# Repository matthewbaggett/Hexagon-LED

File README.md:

# Hexagon LED

## Objective:

Build a small, inexpensive hexagonal lighting PCB with an inexpensive microcontroller that can communicate using slow-speed software serial
 with the other attached nodes and to an optionally fitted ESP8266 ESP-01 module which will designate itself the "host", 
 and populate out colour information from the center.
 
A serial mesh of communication between each interlinked hexagonal node.

A REST service running on the ESP sat on the users Wifi allowing for colour information to be pushed from an app or script.

## Render

## Board

Not shown: Groundplane fill. Represented by area inside red dashed octagon

Purple outline: Lasercut rear plastic panel to insert into the back of a 3d printed housing.

Illustration shows shielded 3x2 keyed connectors, not necessarily fitted.

## Schematic

### Microcontroller

### LEDs

### Interconnects

## License
This project is licensed under the The TAPR Open Hardware License.

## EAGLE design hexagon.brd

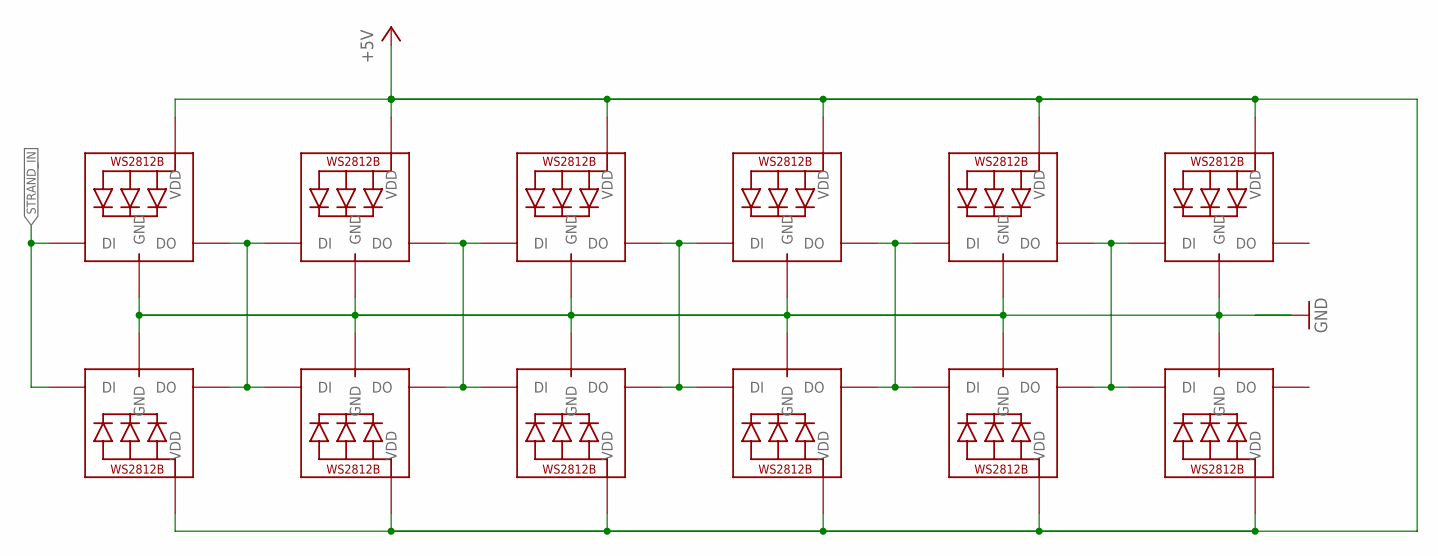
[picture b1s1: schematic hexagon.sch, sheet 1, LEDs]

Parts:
LED1, LED2, LED3, LED4, LED5, LED6: WS2812B5050; WS2812B
LED7, LED8, LED9, LED10, LED11, LED12: WS2812B3535; LED3535

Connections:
+5V: LED1.1-VDD (VDD), LED2.1-VDD (VDD), LED3.1-VDD (VDD), LED4.1-VDD (VDD), LED5.1-VDD (VDD), LED6.1-VDD (VDD), LED7.2 (VDD), LED8.2 (VDD), LED9.2 (VDD), LED10.2 (VDD), LED11.2 (VDD), LED12.2 (VDD); also elsewhere on the board
GND: LED1.3-GND (GND), LED2.3-GND (GND), LED3.3-GND (GND), LED4.3-GND (GND), LED5.3-GND (GND), LED6.3-GND (GND), LED7.4 (GND), LED8.4 (GND), LED9.4 (GND), LED10.4 (GND), LED11.4 (GND), LED12.4 (GND); also elsewhere on the board
unnamed: LED1.4-DIN (DI), LED6.2-DOUT (DO), LED7.1 (DI), LED12.3 (DO)
unnamed: LED2.2-DOUT (DO), LED3.4-DIN (DI), LED8.3 (DO), LED9.1 (DI)
unnamed: LED3.2-DOUT (DO), LED4.4-DIN (DI), LED9.3 (DO), LED10.1 (DI)
unnamed: LED4.2-DOUT (DO), LED5.4-DIN (DI), LED10.3 (DO), LED11.1 (DI)
unnamed: LED5.2-DOUT (DO), LED6.4-DIN (DI), LED11.3 (DO), LED12.1 (DI)
STRAND_IN: LED2.4-DIN (DI), LED8.1 (DI); also elsewhere on the board

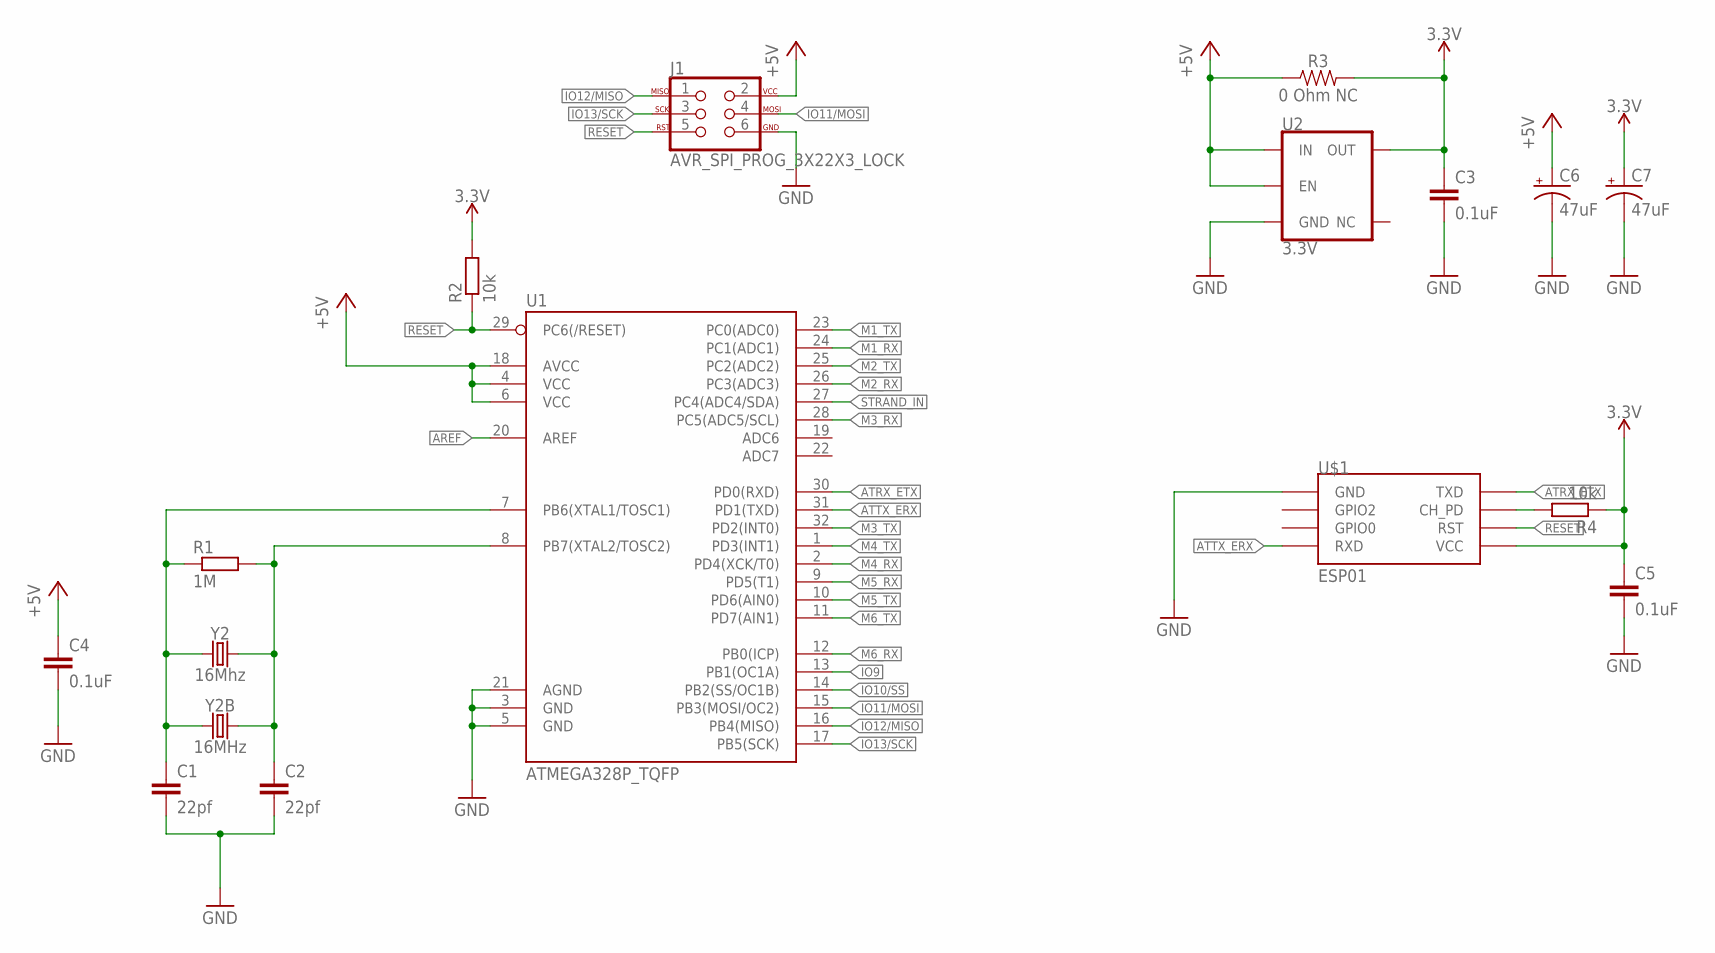
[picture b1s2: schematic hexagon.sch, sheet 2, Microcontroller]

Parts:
C1, C2: 22pf; C0603
C3, C4, C5: 0.1uF; C0603
C6, C7: 47uF; PANASONIC_D
J1: AVR_SPI_PROG_3X22X3_LOCK; 2X3_LOCK
R1: 1M; R0603
R2, R4: 10k; R0603
R3: 0 Ohm NC; 0603
U1: ATMEGA328P_TQFP; TQFP32-08
U2: 3.3V; SOT23-5
U$1: ESP01
Y2: 16Mhz; HC49UP
Y2B: 16MHz; HC49U

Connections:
3.3V: C3.1, C5.1, C7.+, R2.2, R3.2, R4.1, U2.5 (OUT), U$1.VCC
328_OSC1: C1.1, R1.1, U1.7 (PB6(XTAL1/TOSC1)), Y2.1, Y2B.1
328_OSC2: C2.1, R1.2, U1.8 (PB7(XTAL2/TOSC2)), Y2.2, Y2B.2
+5V: C4.1, C6.+, J1.2, R3.1, U1.4 (VCC), U1.6 (VCC), U1.18 (AVCC), U2.1 (IN), U2.3 (EN); also elsewhere on the board
AREF: U1.20 (AREF)
ATRX_ETX: U1.30 (PD0(RXD)), U$1.TX (TXD)
ATTX_ERX: U1.31 (PD1(TXD)), U$1.RX (RXD)
GND: C1.2, C2.2, C3.2, C4.2, C5.2, C6.-, C7.-, J1.6, U1.3 (GND), U1.5 (GND), U1.21 (AGND), U2.2 (GND), U$1.GND; also elsewhere on the board
IO9: U1.13 (PB1(OC1A))
IO10/SS: U1.14 (PB2(SS/OC1B))
IO11/MOSI: J1.4, U1.15 (PB3(MOSI/OC2))
IO12/MISO: J1.1, U1.16 (PB4(MISO))
IO13/SCK: J1.3, U1.17 (PB5(SCK))
M1_RX: U1.24 (PC1(ADC1)); also elsewhere on the board
M1_TX: U1.23 (PC0(ADC0)); also elsewhere on the board
M2_RX: U1.26 (PC3(ADC3)); also elsewhere on the board
M2_TX: U1.25 (PC2(ADC2)); also elsewhere on the board
M3_RX: U1.28 (PC5(ADC5/SCL)); also elsewhere on the board
M3_TX: U1.32 (PD2(INT0)); also elsewhere on the board
M4_RX: U1.2 (PD4(XCK/T0)); also elsewhere on the board
M4_TX: U1.1 (PD3(INT1)); also elsewhere on the board
M5_RX: U1.9 (PD5(T1)); also elsewhere on the board
M5_TX: U1.10 (PD6(AIN0)); also elsewhere on the board
M6_RX: U1.12 (PB0(ICP)); also elsewhere on the board
M6_TX: U1.11 (PD7(AIN1)); also elsewhere on the board
unnamed: R4.2, U$1.CH_PD
RESET: J1.5, R2.1, U1.29 (PC6(/RESET)), U$1.RST
STRAND_IN: U1.27 (PC4(ADC4/SDA)); also elsewhere on the board

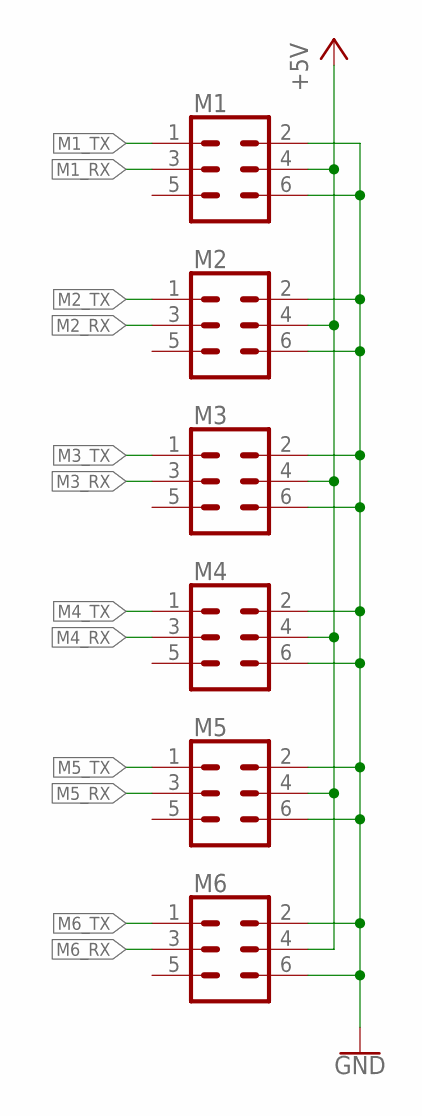
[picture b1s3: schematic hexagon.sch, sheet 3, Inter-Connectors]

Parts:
M1, M2, M3, M4, M5, M6: CONN_03X2SHROUD; 2X3-SHROUDED

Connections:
+5V: M1.4, M2.4, M3.4, M4.4, M5.4, M6.4; also elsewhere on the board
GND: M1.2, M1.6, M2.2, M2.6, M3.2, M3.6, M4.2, M4.6, M5.2, M5.6, M6.2, M6.6; also elsewhere on the board
M1_RX: M1.3; also elsewhere on the board
M1_TX: M1.1; also elsewhere on the board
M2_RX: M2.3; also elsewhere on the board
M2_TX: M2.1; also elsewhere on the board
M3_RX: M3.3; also elsewhere on the board
M3_TX: M3.1; also elsewhere on the board
M4_RX: M4.3; also elsewhere on the board
M4_TX: M4.1; also elsewhere on the board
M5_RX: M5.3; also elsewhere on the board
M5_TX: M5.1; also elsewhere on the board
M6_RX: M6.3; also elsewhere on the board
M6_TX: M6.1; also elsewhere on the board

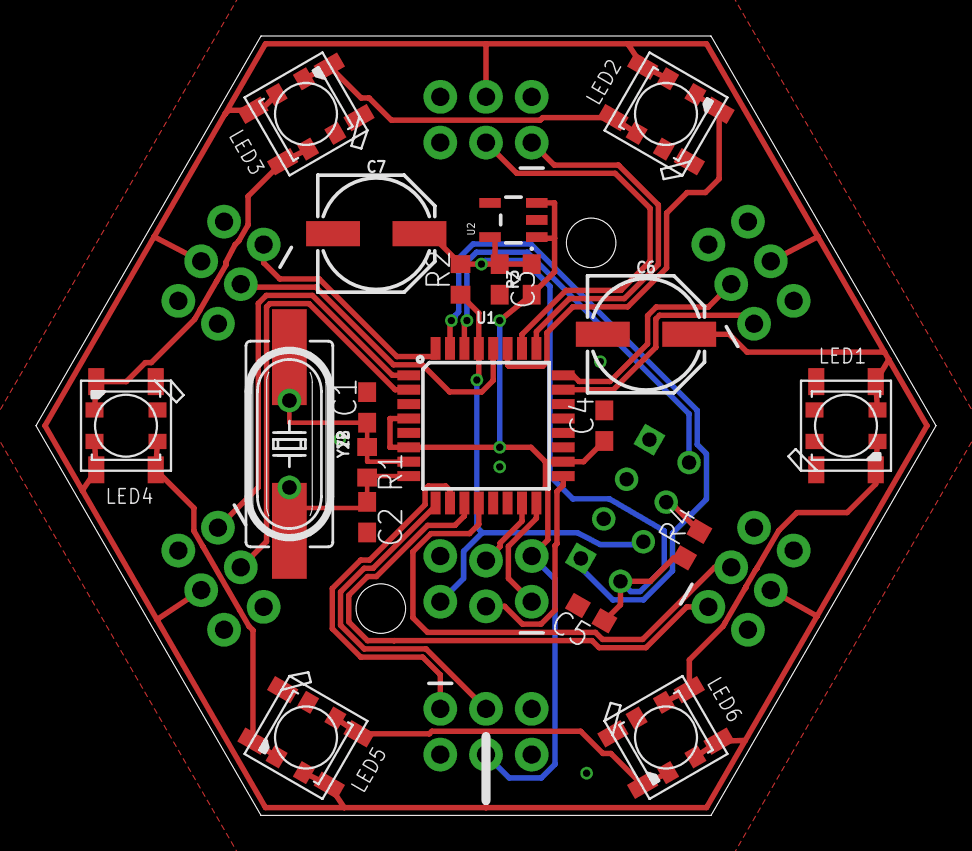
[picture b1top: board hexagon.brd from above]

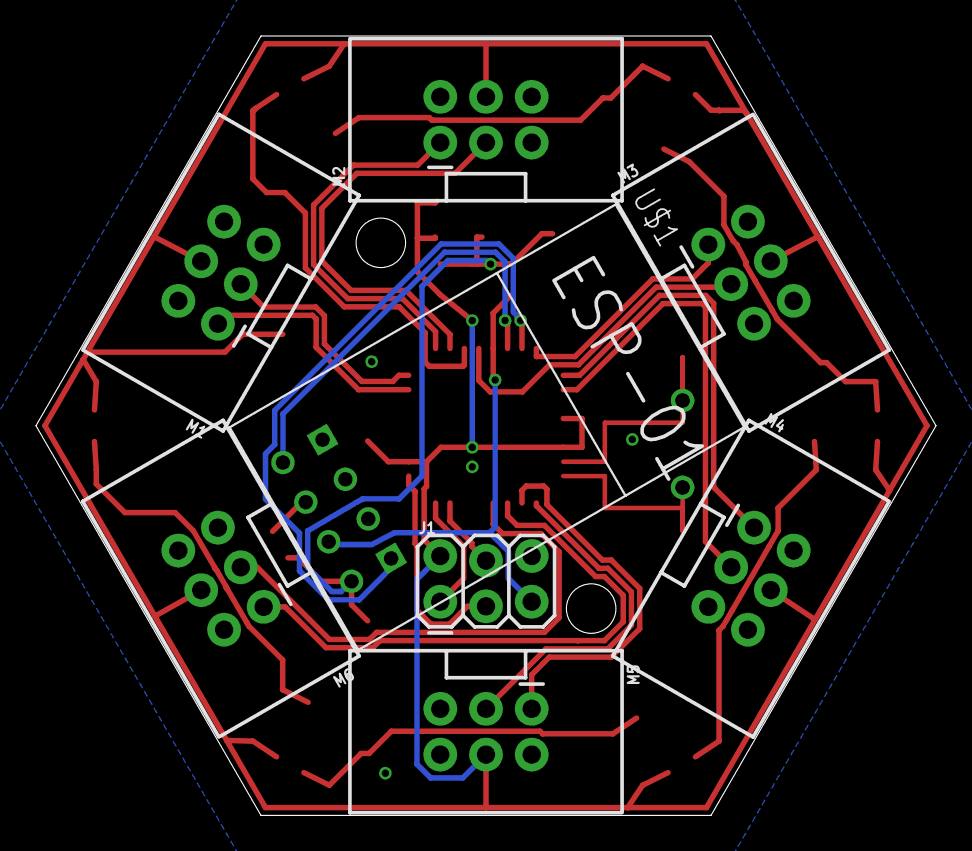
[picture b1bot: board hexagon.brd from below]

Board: 2 copper layers, 50.0 x 43.3 mm, 35 parts (8 on the bottom side), 30 nets.

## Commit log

2019-07-15 Initial layout
2019-07-16 Continuing to work out the layout kinks. Added ESP.
2019-07-16 add render
2019-07-17 Fix continuity of bHousing
2019-08-01 Gussy up with a readme and some renders
2019-08-01 Updated gitignore
2019-08-01 Missed a space.
2019-08-02 Set theme jekyll-theme-leap-day
2019-08-02 Move assets around, fix labels
2019-08-02 set theme

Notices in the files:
parts and their libraries:
SparkFun-IC-Microcontroller: Licensing: Creative Commons ShareAlike 4.0 International - https://creativecommons.org/licenses/by-sa/4.0
